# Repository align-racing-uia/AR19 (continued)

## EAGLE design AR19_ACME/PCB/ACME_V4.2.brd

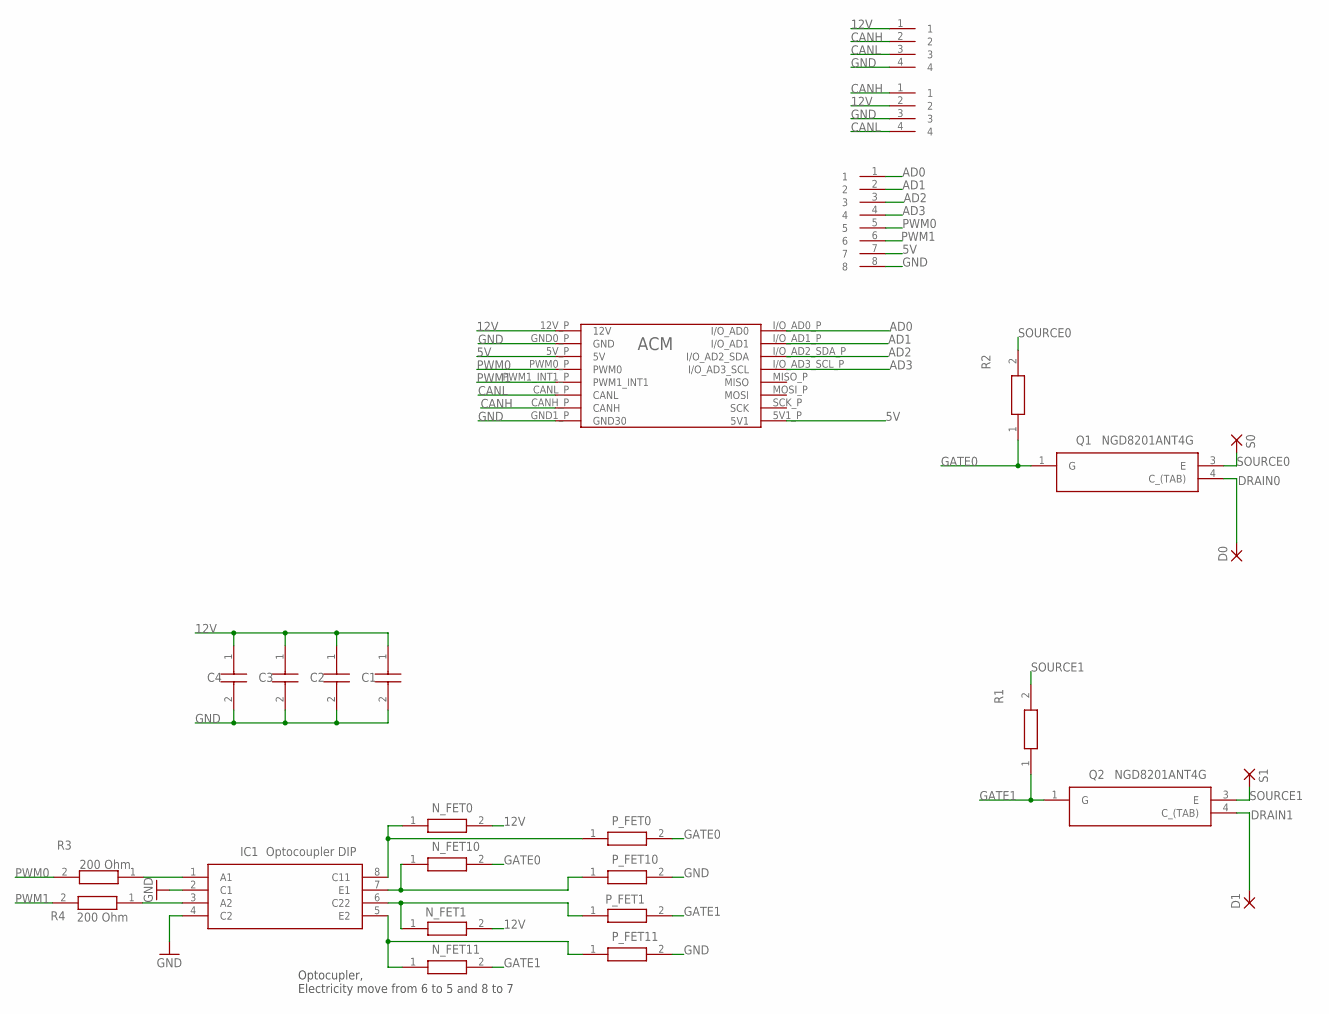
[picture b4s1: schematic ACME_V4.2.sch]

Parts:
C1, C2, C3, C4: TACL105K006XTA; CAPPC1709X100N
D0, D1: WIREPADSMD5-2,5; 5-2,5
IC1: Optocoupler DIP; DIP762W60P254L966H485Q8N
N_FET0, N_FET1, N_FET10, N_FET11: ERA-3AEB2262V; RESC1608X55N
P_FET0, P_FET1, P_FET10, P_FET11: ERA-3AEB2262V; RESC1608X55N
Q1, Q2: NGD8201ANT4G; TO229P990X238-4N
R1, R2: ERA-3AEB2262V; RESC1608X55N
R3, R4: 200 Ohm; RESC1608X55N
S0, S1: WIREPADSMD5-2,5; 5-2,5
U$1: ACM_CASTELLATED; ACM_CAS_FP
U$3, U$4, U$5: 16P_CONNECTOR; 16P_CONNECTOR_FP

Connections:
5V: U$1.5V1_P (5V1), U$1.5V_P (5V), U$5.7
12V: C1.1 (+), C2.1 (+), C3.1 (+), C4.1 (+), N_FET0.2, N_FET1.2, U$1.12V_P (12V), U$3.1, U$4.2
AD0: U$1.I/O_AD0_P (I/O_AD0), U$5.1
AD1: U$1.I/O_AD1_P (I/O_AD1), U$5.2
AD2: U$1.I/O_AD2_SDA_P (I/O_AD2_SDA), U$5.3
AD3: U$1.I/O_AD3_SCL_P (I/O_AD3_SCL), U$5.4
CANH: U$1.CANH_P (CANH), U$3.2, U$4.1
CANL: U$1.CANL_P (CANL), U$3.3, U$4.4
DRAIN0: D0.1, Q1.4 (C_(TAB))
DRAIN1: D1.1, Q2.4 (C_(TAB))
GATE0: N_FET10.2, P_FET0.2, Q1.1 (G), R2.1
GATE1: N_FET11.2, P_FET1.2, Q2.1 (G), R1.1
GND: C1.2 (-), C2.2 (-), C3.2 (-), C4.2 (-), IC1.2 (C1), IC1.4 (C2), P_FET10.2, P_FET11.2, U$1.GND0_P (GND), U$1.GND1_P (GND30), U$3.4, U$4.3, U$5.8
unnamed: IC1.1 (A1), R3.1
unnamed: IC1.8 (C11), N_FET0.1, P_FET0.1
unnamed: IC1.6 (C22), N_FET1.1, P_FET1.1
unnamed: IC1.3 (A2), R4.1
unnamed: IC1.5 (E2), N_FET11.1, P_FET11.1
unnamed: IC1.7 (E1), N_FET10.1, P_FET10.1
PWM0: R3.2, U$1.PWM0_P (PWM0), U$5.5
PWM1: R4.2, U$1.PWM1_INT1_P (PWM1_INT1), U$5.6
SOURCE0: Q1.3 (E), R2.2, S0.1
SOURCE1: Q2.3 (E), R1.2, S1.1

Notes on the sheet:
Optocupler, Electricity move from 6 to 5 and 8 to 7

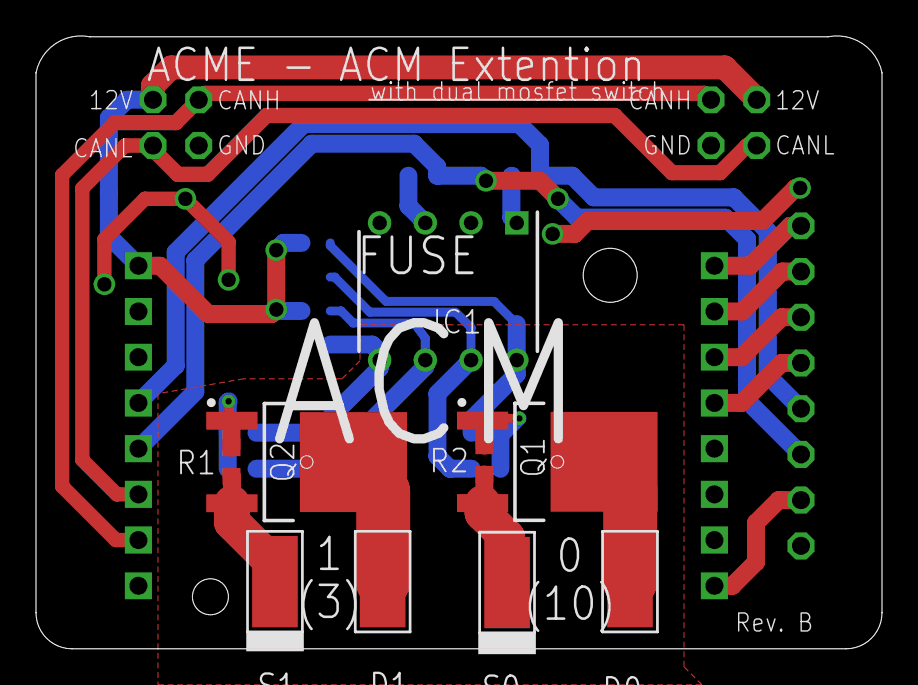
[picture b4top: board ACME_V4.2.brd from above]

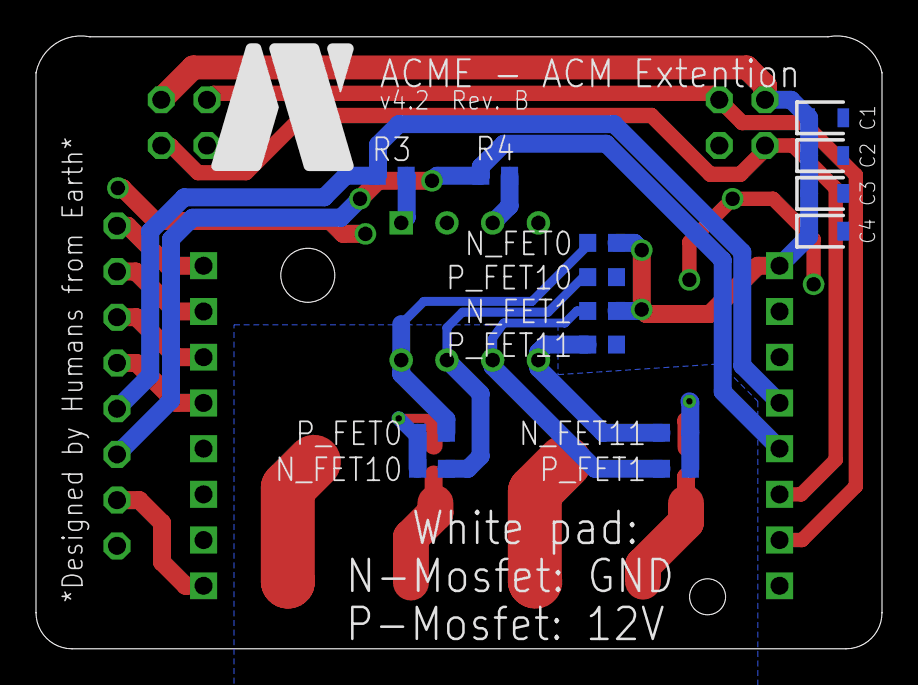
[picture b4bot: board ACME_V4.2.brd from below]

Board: 2 copper layers, 47.0 x 34.0 mm, 27 parts (14 on the bottom side), 23 nets.

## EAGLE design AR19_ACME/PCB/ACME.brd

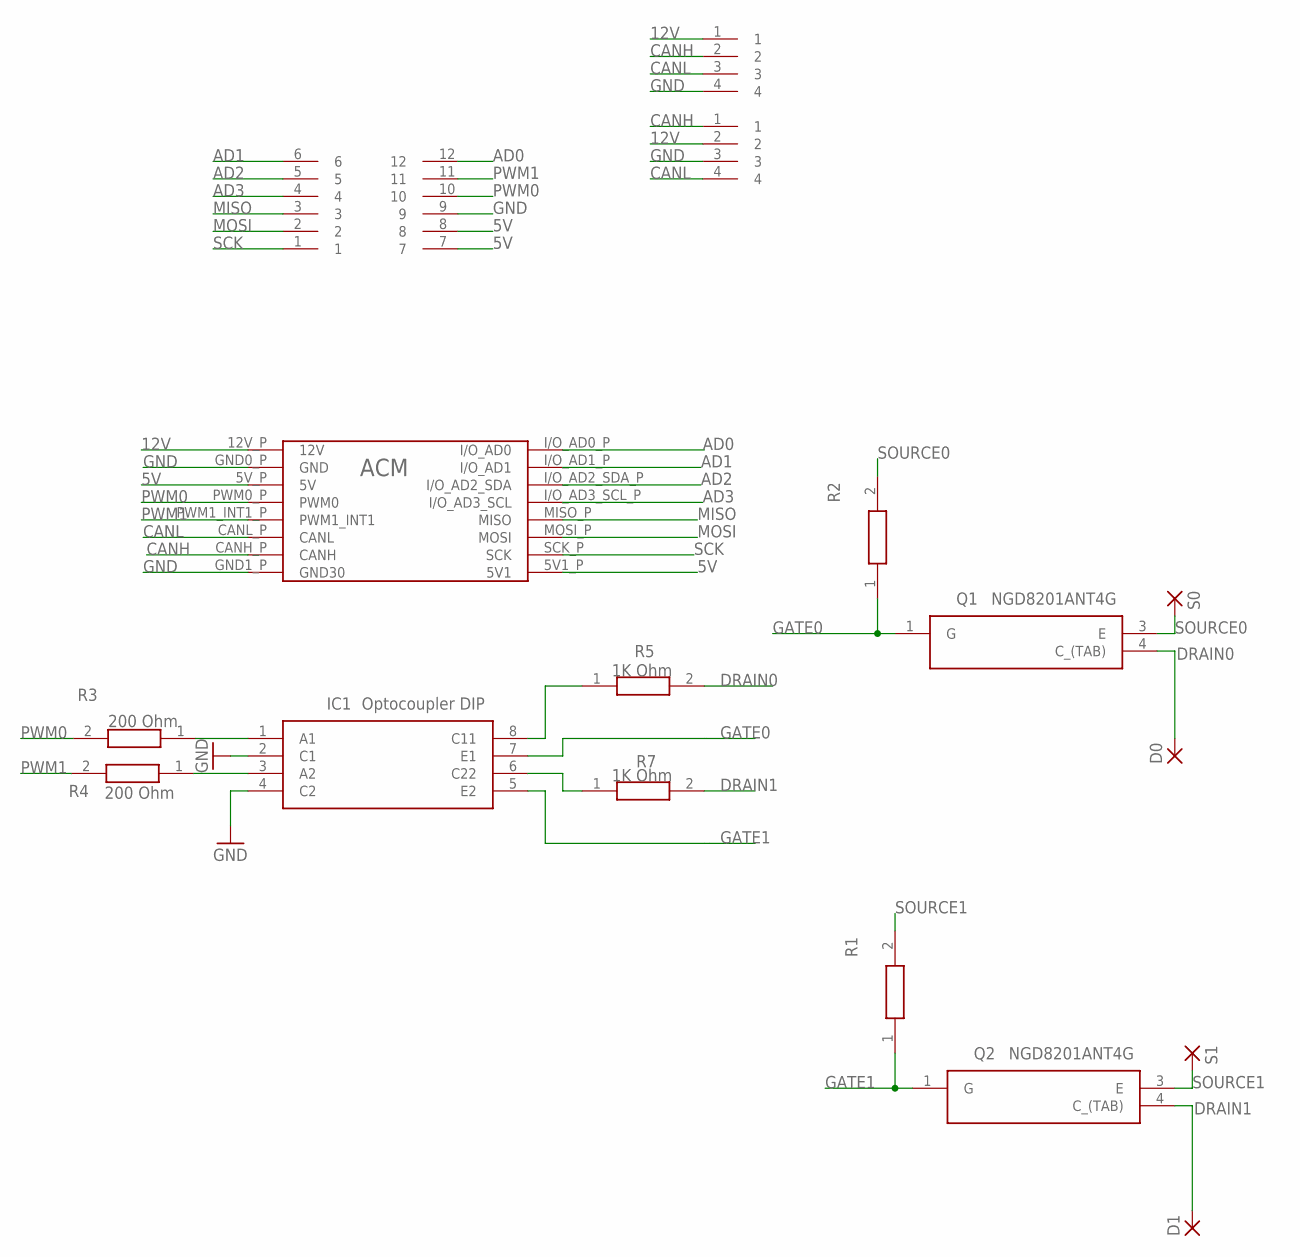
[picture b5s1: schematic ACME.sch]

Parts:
D0, D1: WIREPADSMD5-2,5; 5-2,5
IC1: Optocoupler DIP; DIP762W60P254L966H485Q8N
Q1, Q2: NGD8201ANT4G; TO229P990X238-4N
R1, R2: ERA-3AEB2262V; RESC1608X55N
R3, R4: 200 Ohm; RESC1608X55N
R5, R7: 1K Ohm; RESC1608X55N
S0, S1: WIREPADSMD5-2,5; 5-2,5
U$1: ACM_CASTELLATED; ACM_CAS_FP
U$2, U$3, U$4: 16P_CONNECTOR; 16P_CONNECTOR_FP

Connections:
5V: U$1.5V1_P (5V1), U$1.5V_P (5V), U$2.7, U$2.8
12V: U$1.12V_P (12V), U$3.1, U$4.2
AD0: U$1.I/O_AD0_P (I/O_AD0), U$2.12
AD1: U$1.I/O_AD1_P (I/O_AD1), U$2.6
AD2: U$1.I/O_AD2_SDA_P (I/O_AD2_SDA), U$2.5
AD3: U$1.I/O_AD3_SCL_P (I/O_AD3_SCL), U$2.4
CANH: U$1.CANH_P (CANH), U$3.2, U$4.1
CANL: U$1.CANL_P (CANL), U$3.3, U$4.4
DRAIN0: D0.1, Q1.4 (C_(TAB)), R5.2
DRAIN1: D1.1, Q2.4 (C_(TAB)), R7.2
GATE0: IC1.7 (E1), Q1.1 (G), R2.1
GATE1: IC1.5 (E2), Q2.1 (G), R1.1
GND: IC1.2 (C1), IC1.4 (C2), U$1.GND0_P (GND), U$1.GND1_P (GND30), U$2.9, U$3.4, U$4.3
MISO: U$1.MISO_P (MISO), U$2.3
MOSI: U$1.MOSI_P (MOSI), U$2.2
unnamed: IC1.1 (A1), R3.1
unnamed: IC1.3 (A2), R4.1
unnamed: IC1.8 (C11), R5.1
unnamed: IC1.6 (C22), R7.1
PWM0: R3.2, U$1.PWM0_P (PWM0), U$2.10
PWM1: R4.2, U$1.PWM1_INT1_P (PWM1_INT1), U$2.11
SCK: U$1.SCK_P (SCK), U$2.1
SOURCE0: Q1.3 (E), R2.2, S0.1
SOURCE1: Q2.3 (E), R1.2, S1.1

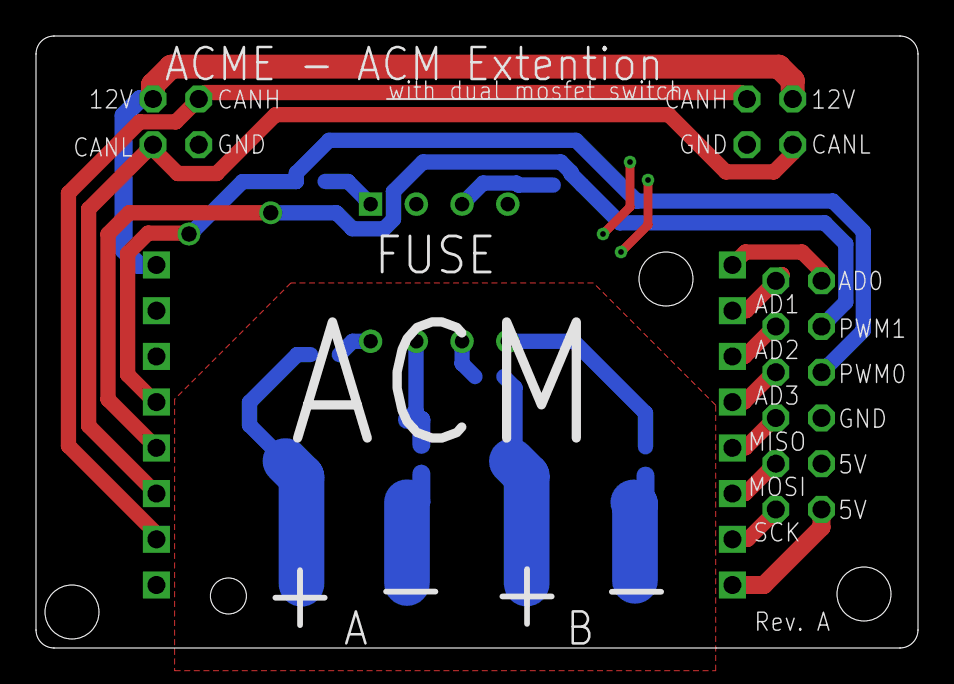
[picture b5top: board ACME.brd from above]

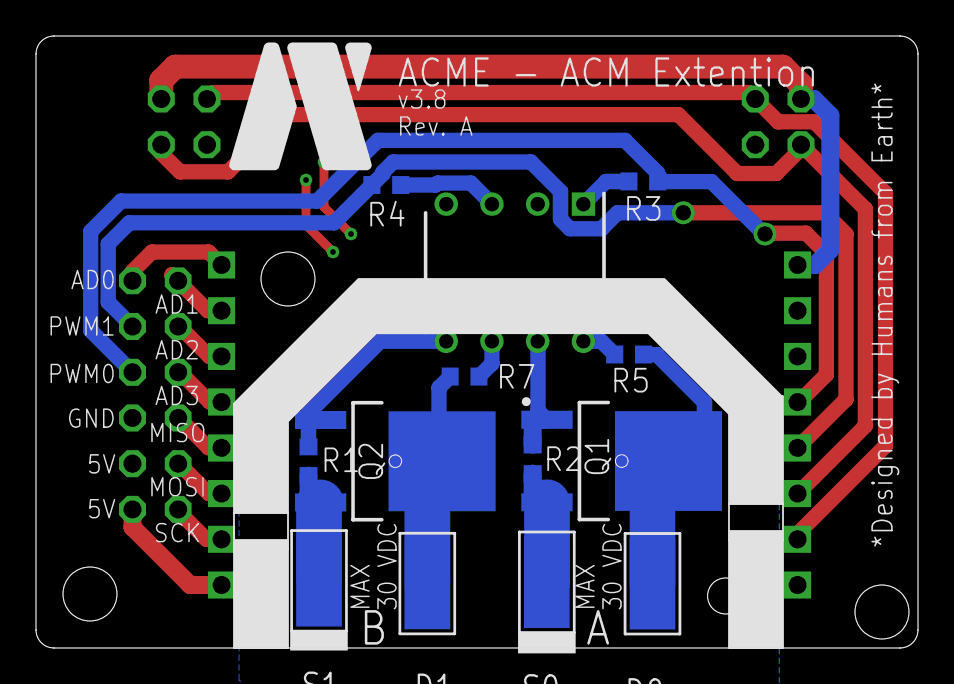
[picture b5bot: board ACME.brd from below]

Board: 2 copper layers, 49.0 x 34.0 mm, 17 parts (13 on the bottom side), 24 nets.

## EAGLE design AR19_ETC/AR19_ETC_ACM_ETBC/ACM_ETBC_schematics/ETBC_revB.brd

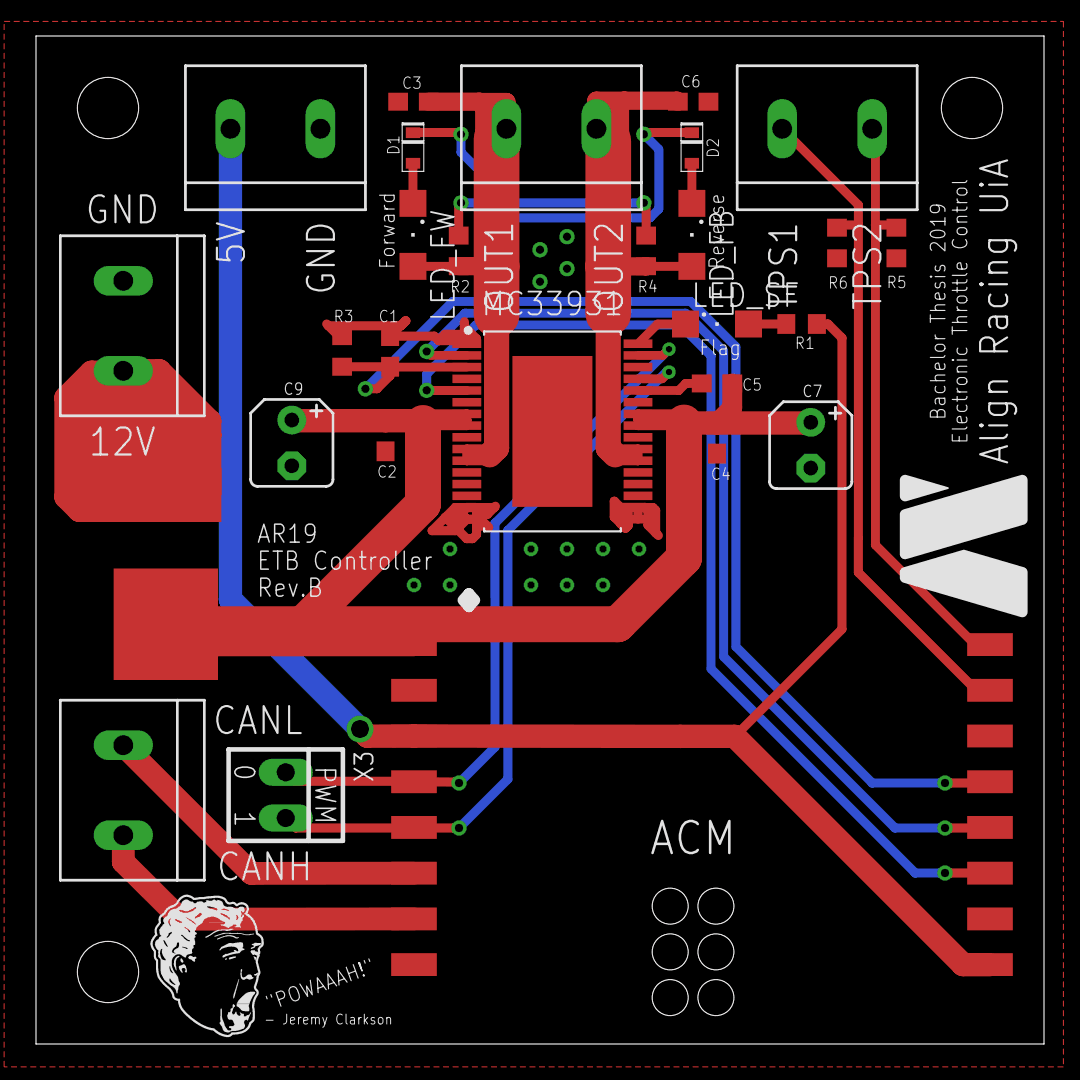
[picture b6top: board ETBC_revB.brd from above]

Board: 2 copper layers, 56.0 x 56.0 mm, 28 parts (0 on the bottom side), 22 nets.

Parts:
C1: 0.047 μF; C0603
C2, C4: 100 nF; C0603
C3, C6: 10 nF; C0603
C5: 33 nF; C0603
C7, C9: 47 μF; B45181A
D1, D2: CDBU0340-HFCDBU0340-HF; DIOM1709X85
D3: MBRD1045; DPAK
LED_FB: YLW; SML1206
LED_FW: GRN; SML1206
LED_SF: RED; SML1206
MC33931: MC33931; SOP65P1030X245-33T480X861
R1: 4.7 kΩ; R0603
R2, R4, R5, R6: 10 kΩ; R0603
R3: 270 Ω; R0603
U$1, U$2, U$5, U$6, U$7: 2PIN_TERMINAL_BLOCK
U$3: ACM_CASTELLATED; ACM_CAS_FP
X3: 22-23-2021

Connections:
5V: R1.2, U$3.5V, U$3.5V1, U$6.P$1
12V: D3.P$1, D3.P$3, U$2.P$1
CANH: U$1.P$1, U$3.CANH
CANL: U$1.P$2, U$3.CANL
D1: MC33931.2, U$3.MISO
ENABLE/D2: MC33931.5, U$3.MOSI
FEEDBACK: C1.1, MC33931.3, R3.2, U$3.I/O_AD3_SCL
GND: C1.2, C2.2, C3.2, C4.2, C6.2, C7.-, C9.-, MC33931.1, MC33931.15, MC33931.16, MC33931.17, MC33931.18, MC33931.33, R3.1, R5.2, R6.2, U$2.P$2, U$3.GND, U$3.GND30, U$6.P$2
unnamed: LED_SF.A, R1.1
unnamed: LED_SF.C, MC33931.32
unnamed: D2.2$A, LED_FB.C
unnamed: C5.1, MC33931.28
unnamed: D1.2$A, LED_FW.C
unnamed: D1.1$K, R4.1
unnamed: D2.1$K, R2.1
OUT1: C3.1, LED_FW.A, MC33931.10, MC33931.11, R2.2, U$5.P$1
OUT2: C6.1, LED_FB.A, MC33931.22, MC33931.23, R4.2, U$5.P$2
PWM0: MC33931.31, U$3.PWM0, X3.1
PWM1: MC33931.29, U$3.PWM1_INT1, X3.2
TPS1: R5.1, U$3.I/O_AD0, U$7.P$2
TPS2: R6.1, U$3.I/O_AD1, U$7.P$1
VPWR: C2.1, C4.1, C5.2, C7.+, C9.+, D3.P$4, MC33931.7, MC33931.8, MC33931.25, MC33931.26, U$3.12V

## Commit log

2019-04-16 ADded file structure
2019-04-16 Added folders
2019-04-16 added structure for Shutdown ACM
2019-04-16 added more files to shutdown ACM
2019-04-16 added functionality to Shutdown ACM
2019-04-16 forgot to save
2019-04-16 Created AR19_ACM
    Created ACM library
2019-04-16 Rule fix
    Added "SUBPROJECT" in structure rules
2019-04-17 added acmPing
2019-04-17 fixed canbus
2019-04-18 final ping functionality canbus
2019-04-20 Add files via upload
    Utfør fikser i hennhold til todo.txt
    Implementert brukersystem og mulighet for å endre enkelte IC-verdier over CANbus, ref: ICmodificationComands.txt
2019-04-20 Sma endringer
2019-04-21 Commiting fra PlatformIO
2019-04-21 Mindre fiks, ref todo-log
2019-04-22 endrett pin til kutting
2019-04-22 Lagt til dokumentasjon for pinout, samt samlet tillegsdokumenter i egen mappe "/dokumentation"
2019-04-23 Lagt til Demoprogram for simulering av RPM og girskift til avduking
2019-04-23 endret Demo til .ino
2019-04-24 endrett verdier i demo
2019-04-24 Demo av display er nå ferdig
2019-04-25 Liten tuning av demoen
2019-04-26 Added: ACM PCB files, images and datasheets
2019-04-26 Added: Newest ACM PCB
2019-04-26 Created PCB readme
2019-04-26 Added: Change log
2019-04-26 Moved: Schematic images
2019-04-27 Added: Breaklight
2019-04-28 satt shutdownpin høg
2019-04-28 fixed dash acm - mangla litt på canbus
2019-04-29 Added EGS to git
2019-04-29 kexed canbus on gear acm and added retard
2019-04-29 EGS RETARD OK
2019-04-29 qwert
2019-04-29 added shutdown functionality
2019-04-30 Arduino json file
2019-04-30 added code for steering wheel acm
2019-04-30 gear acm fixes
2019-05-03 Added: ACME (Old boards)
2019-05-03 Changed Readme.md
2019-05-04 Added: ACME
2019-05-04 ACME ready for production
2019-05-05 Generated Gerber for ACME V4
2019-05-05 ACME V4.2
2019-05-05 ACME_V4.2
2019-05-07 clutch ok
2019-05-09 Sma andringer
2019-05-09 ACME Ordered
2019-05-09 Setting contstants
2019-05-10 Update main.cpp
    Mindre endringer
2019-05-13 ETC Initial commit
2019-05-13 Modified description of headers
2019-05-13 Removed testing lines in code
2019-05-13 Changed TPS1,2 max/min values
2019-05-14 Updated trace figures. Added thermal analysis of ETBC
2019-05-16 Updated BSPD technical drawings
2019-05-20 Oppdateringer for å være i hennold til Bachelor og komunikasjon med ETC
2019-05-20 Implemented Launch Control functionality
2019-05-20 div vscode
2019-05-24 Modified ETBC code
2019-05-25 La til Hallefect code
2019-05-25 La til rattACM
2019-05-27 fixed
2019-05-27 usikker
2019-05-27 Uncommented additional functionality
2019-05-27 Har lagt inn PID-parametere for RPM-regulering. KOmunikasjon med ETC er oppdatert.
2019-05-28 Added errer telemetry to EGS
2019-05-28 Mindre bugfix
2019-05-29 Shutdown code @ 500kbps
2019-05-29 Modified bit rate
2019-05-29 Breaklight code @ 500Kbps
2019-05-30 Oppdatert systemet for å ta imot RPM meldinger fra ECu'en
2019-05-30 Minor modifications and chaged CAN-bus bit rate
2019-05-30 Commented out 0x666
2019-05-30 qwerty
2019-05-30 EGS functional
2019-05-31 Har lagt til motor RPM-klasse
2019-05-31 Oppdatert Hall-kode og Ratt-kode
2019-05-31 Changed idle position
2019-05-31 Revert "Merge branch 'master' of https://github.com/align-racing-uia/AR19"
    This reverts commit f67d6620a99e78caf0fb3195ba17fbafa4a74a34, reversing
    changes made to 7fdd36714a724812e5f8b2e3eef0897d370050e9.
2019-05-31 Updated since git fucke up
2019-06-05 Added more functionality to EGS
2019-06-08 Updated ETBC and Pedalbox code to current
2019-06-08 Added RevE BSPD
2019-06-09 Added shutdown in accorance with FMEA
2019-06-09 jncksdnf
2019-06-09 Added shutdown to ping functionality
2019-06-09 Complete Upload
    Complete upload of earlier revisions of Steering Wheel ACM
2019-06-09 Name Change
    ...
2019-06-09 Feilsoking av EGS-kode
2019-06-09 Added CAD drawings of BSPD RevE
2019-06-09 Removed Duplicate & Added Ping function
2019-06-09 Updated to v2.1
    Added implausibility check for TPS and timeout functions for ETBC.
    Added implausibility check for APPS and BPS for Pedalbox.
2019-06-10 Sikkerhetsfunksjon er lagt til i MainBoard
2019-06-17 Lagt inn 'hand-shake'-conditions mot ETC og EGS og feilhåndtering av disse
2019-06-17 added
2019-06-17 added semicolon
2019-06-17 Neutral functional - locks up if neutral not reached
    N
2019-06-18 shutdown fix
2019-06-18 lnlfe
2019-06-18 fixed gearUp telemetry and shutdown signal timer
2019-06-18 added revision
2019-06-19 massive EGS fix
2019-06-19 Update f_SensorData.ino
    asd
2019-06-21 Redigert idle posisjon til etbc og kommentert vekk implausability på TPS1 og TPS 2 så det skal funke med ECU'en
2019-06-21 Created: Brakelight code V2
2019-06-22 Updated Wheel Speed Sensors
2019-06-22 strcturing and added functionality
2019-06-24 bfeibf
2019-06-24 fekk kompilere no
2019-06-26 added LC and fallback solution to 2nd gear. NB CLUTCH DOES NOT WORK - BUT NOT BECAUSE OF CODE
2019-07-02 Added functionality - commented away clutch pressure
2019-07-03 Added cluthpressure to upshift
2019-07-04 Har lagt til ny ratt-kode
2019-07-05 Added new developed version of EGS.
    To be completed.
2019-07-05 Implemented functionality for calibrating EGS.
    Sends two bytes of sensor values when set to calibrate mode: gear voltage sensor and clutch pressure.
2019-07-05 Added functions for shift up and down
2019-07-06 Modified ETBC and Brakelight code
2019-07-06 Uncommented implausibility
2019-07-07 Commented out pedalbox implausibility check and slightly modified calibration
2019-07-08 Fixed implausibility check. Added variable for imp. margins.
2019-07-08 Added shift to neutral. Added clutch pressure checks at downshift and 1st to 2nd.
2019-07-08 . kalibrert apps og bps
2019-07-08 Split EGS code into MC and car gearing.
    Traditional MC gearing (1-N-2-...) and car gearing ( N-1-2-...)
2019-07-08 Calibrated TPS
2019-07-08 Trying to fix implausibility
2019-07-08 Now possible to shift from neutral down to first
2019-07-08 Minor modifications to implausibilitycheck
2019-07-08 Nøytralkanpp og pljesensorer
